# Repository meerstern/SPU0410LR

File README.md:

# SPU0410LR
The Converter board of Kicad Data for SPU0410LR5H

## 概要

Knowles社製の[アナログ出力MEMSマイクSPU0410LR5H][1]を2.54mmピッチへ変換する基板です。  
可聴音から超音波(100Hz～80kHz)までの幅広い帯域を高感度にセンシングすることが可能です。  
超音波センサや超音波通信などに使用可能です。  
マイク穴は基板裏面の丸印部分です。  
電源電圧1.5V~3.6V

## 超音波マイク比較
 用途に応じて様々な製品をラインアップしています  
| 製品名 | インタフェース | アンプ搭載有無 | 用途 | 
|:-----------|:------------|:------------|:------------|
| [アナログ出力マイク(本製品)][A] | アナログ | 無 | 任意のアンプ回路を使用したい場合 | 
| [可変アンプ内蔵アナログ出力マイク][B] | アナログ | 有(可変1~50倍) | 増幅率の調整が必要な場合 |	
| [アンプ内蔵アナログ出力マイク][C] |	アナログ | 有(固定50倍) | 一定した増幅が必要な場合	| 
| [デジタル出力マイク][D] |	デジタルPDM | 不要 | フルデジタルで実装する場合やワイドレンジが必要な場合 | 

## 販売サイト
  * [スイッチサイエンス][2]

## 告知
SPU0410LR5Hの生産完了に伴い、後継品の[SPV0142LR5H][3]に移行しました(26年3月)。

License - MIT

[1]: https://www.digikey.jp/product-detail/ja/knowles/SPU0410LR5H-QB-7/423-1139-1-ND/2420983 "*1"
[2]: https://www.switch-science.com/products/3378
[3]: https://github.com/meerstern/SPV0142LR5H

[A]: https://github.com/meerstern/SPU0410LR
[B]: https://github.com/meerstern/SPU0410LR_with_VariableAmp
[C]: https://github.com/meerstern/SPU0410LR_with_Amp
[D]: https://github.com/meerstern/SPH0641LU

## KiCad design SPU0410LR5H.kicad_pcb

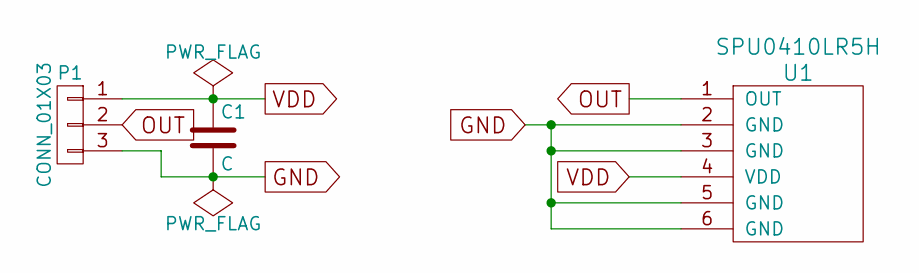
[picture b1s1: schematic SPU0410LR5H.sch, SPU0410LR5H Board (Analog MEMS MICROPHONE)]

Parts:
C1: C; generic-SMD1608
P1: CONN_01X03; pinhead-1X03
U1: SPU0410LR5H

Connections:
GND: C1.2, P1.3, U1.2 (GND), U1.3 (GND), U1.5 (GND), U1.6 (GND)
OUT: P1.2, U1.1 (OUT)
VDD: C1.1, P1.1, U1.4 (VDD)

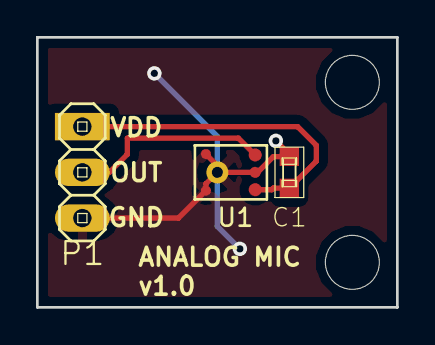
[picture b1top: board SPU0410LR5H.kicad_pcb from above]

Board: 2 copper layers, 20.0 x 15.0 mm, 5 parts (0 on the bottom side), 3 nets.

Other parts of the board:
REF1, REF2: MountingHole_3mm

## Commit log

2017-04-30 init
2022-12-06 Add shop link
